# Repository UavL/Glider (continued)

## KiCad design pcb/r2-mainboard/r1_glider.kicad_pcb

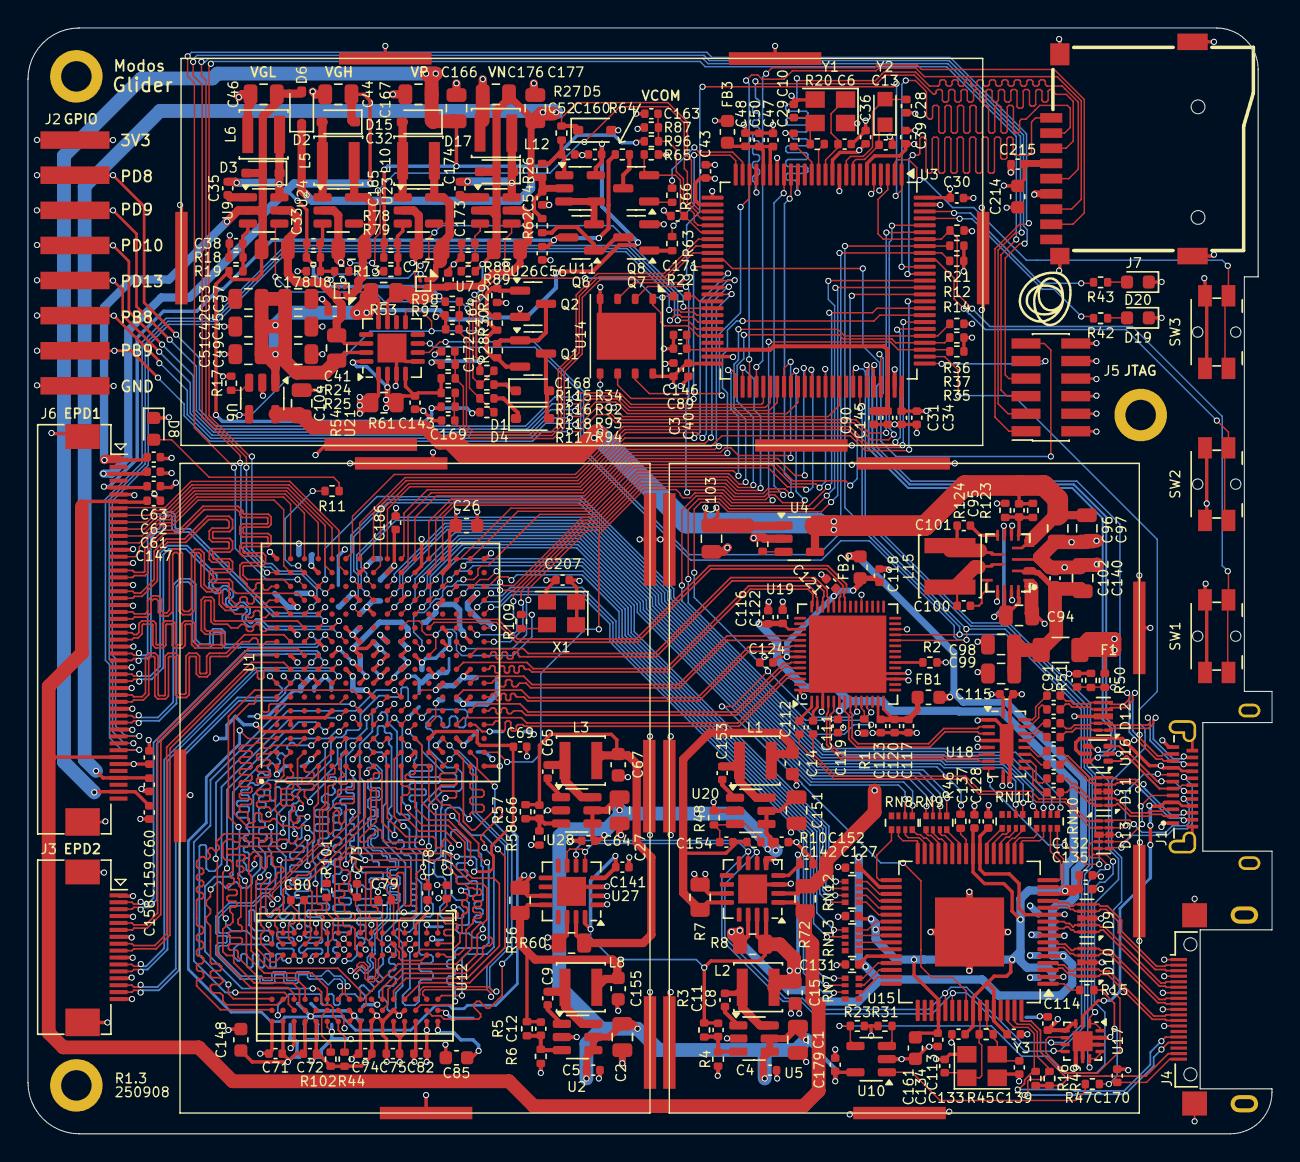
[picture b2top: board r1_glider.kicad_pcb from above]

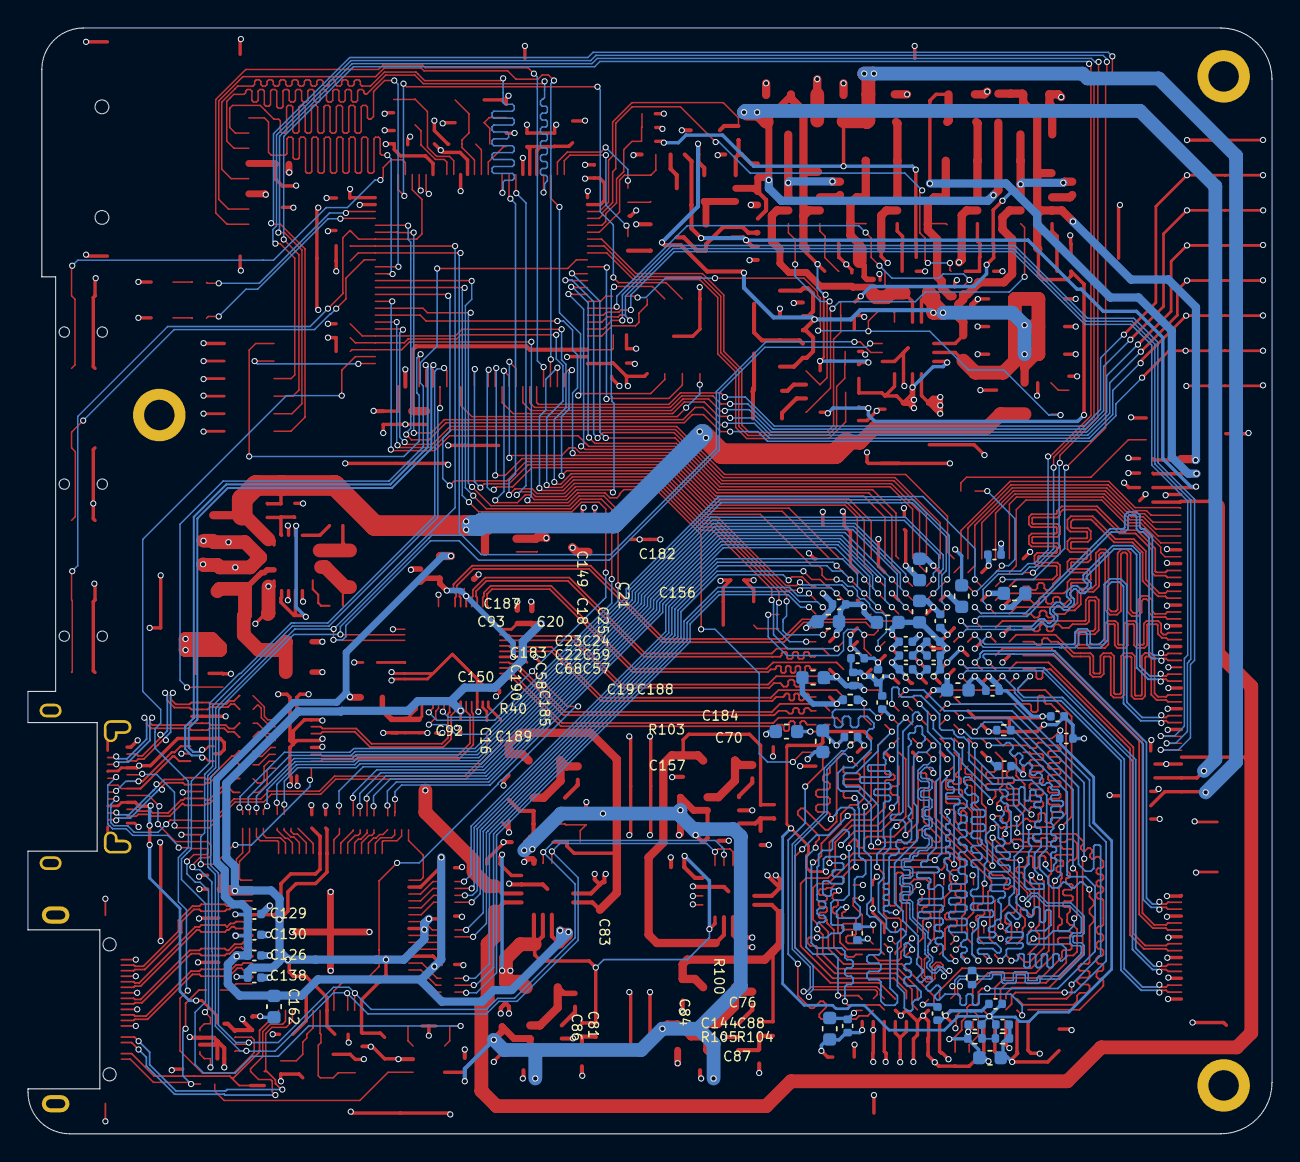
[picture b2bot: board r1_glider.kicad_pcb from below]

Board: 4 copper layers, 90.0 x 80.0 mm, 378 parts (46 on the bottom side), 356 nets.

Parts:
C1, C2, C17, C27, C32, C37, C42, C45, C49, C51, C53, C94, C96, C97, C103, C104, C151: 22uF/10V; C_0805_2012Metric
C3, C4, C5, C7, C8, C9, C29, C30, C31, C35, C36, C39, C40, C43, C48, C50, C54, C55, C60, C61, C62, C63, C64, C65, C71, C72, C74, C75, C76, C77, C78, C88, C100, C101, C102, C105, C106, C107, C108, C109, C110, C111, C112, C114, C115, C119, C120, C121, C122, C123, C124, C127, C128, C129, C130, C131, C133, C134, C135, C136, C137, C138, C139, C141, C142, C143, C144, C147, C152, C153, C158, C159, C160, C171, C174, C179, C215: 100nF/50V; C_0402_1005Metric
C6, C10, C11, C12, C13, C28, C38, C41, C66, C113, C125, C154, C165, C175: 18pF/50V; C_0402_1005Metric
C14, C15, C16, C18, C19, C20, C21, C26, C67, C85, C86, C87, C92, C93, C148, C149, C150, C155, C156, C161, C162, C214: 22uF/6.3V; C_0603_1608Metric
C22, C23, C24, C34, C47, C56, C57, C59, C89, C90, C116, C117, C118, C126, C132, C145, C146, C157, C182, C183, C184: 4.7uF/6.3V; C_0402_1005Metric
C25, C52, C58, C68, C69, C70, C73, C79, C80, C81, C82, C83, C84, C172, C178, C185, C186, C187, C188, C189, C190, C207: 470nF/25V; C_0402_1005Metric
C33, C44, C46, C98, C99, C140, C166, C167, C173, C176, C177: 4.7uF/50V; C_0805_2012Metric
C91, C95, C170: 1nF/50V; C_0402_1005Metric
C163, C164, C168, C169: 1nF/25V; C_0402_1005Metric
D1, D2, D3, D4, D5, D6, D15, D17: 1N5819WS; D_SOD-323_Alt
D8, D19: LED GREEN; LED_0603_1608Metric
D9, D10, D11, D12, D13: RCLAMP0524P; Diodes_UDFN-10_1.0x2.5mm_P0.5mm
D20: LED RED; LED_0603_1608Metric
F1: 3A; Fuse_1206_3216Metric
FB1, FB2, FB3: 120R@100M; L_0603_1608Metric
H1, H3, H4: MountingHole; MountingHole_2.2mm_M2_DIN965_Pad
H5, H6, H7, H8, H9, H12, H13, H14, H15, H16, H17, H18, H19, H20, H21, H22, H23, H25, H26: ICSRC6508-030SFR
J1: GT-USB-7007A; USB_C_Receptacle_GT-USB-7007A
J2: Conn_01x08_MountingPin; 8P_2.54
J3: FPC-05F-16PH20; Xunpu_FPC-05F-16PH20_1x16-1MP_P0.50mm_Horizontal
J4: HDMI_C_1.3; HDMI_C_GT-HD006A-CGNGX
J5: 2x6_1.27_HDR; PinSocket_2x06_P1.27mm_Vertical_SMD
J6: FPC-05F-50PH20; Xunpu_FPC-05F-50PH20_1x50-1MP_P0.50mm_Horizontal
J7: MICRO_SD(TFC-WPAPR-08); TFC-WPAPR-08
L1, L2, L3, L5, L6, L8, L10, L12: WPN3012H4R7MT; L_Changjiang_FNR3012S
L15: WPN4020H2R2MT; L_Changjiang_FNR4020S
Q1, Q7, Q8: AO3401A; SOT-23
Q2: S8050; SOT-23
Q6: AO3400A; SOT-23
R1, R2, R9, R29, R30, R35, R36, R44, R101, R103: 5.1K/1%; R_0402_1005Metric
R3, R13, R26, R28, R34, R51, R57, R58, R62, R87, R92, R93, R94, R97, R116, R118, R124: 100K/1%; R_0402_1005Metric
R4, R25, R27, R64, R89: 22K/1%; R_0402_1005Metric
R5, R78: 150K/1%; R_0402_1005Metric
R6, R48: 120K/1%; R_0402_1005Metric
R7, R8, R53, R54, R56, R60, R61, R72: 20mR; R_0805_2012Metric
R10, R18: 240K/1%; R_0402_1005Metric
R11, R12, R14, R16, R17, R19, R21, R23, R31, R42, R47, R49, R65: 10K/1%; R_0402_1005Metric
R15, R40, R100: 100R/1%; R_0402_1005Metric
R20, R22, R37, R43, R104, R105: 1K/1%; R_0402_1005Metric
R24, R88: 390K/1%; R_0402_1005Metric
R45, R50, R96, R98, R115, R117: 1M/1%; R_0402_1005Metric
R46, R63, R66, R109: 33R/1%; R_0402_1005Metric
R79: 13K/1%; R_0402_1005Metric
R102: 240R/1%; R_0402_1005Metric
R123: 470K/1%; R_0402_1005Metric
RN7, RN8, RN9, RN10, RN11, RN12, RN13: 33R / 4D02WGF330JTCE; R_Array_Convex_4x0402
SW1, SW2, SW3: SW; Panasonic_EVQPUL_EVQPUC
U1: XC6SLX-FTG256; Xilinx_FTG256
U2, U5, U20, U28: SY8113C; TSOT-23-6
U3: STM32H750VBTx; LQFP-100_14x14mm_P0.5mm
U4, U6, U10: MT9700; SOT-23-5
U7, U8: TPS22914BYFPR; WLP-4_0.83x0.83mm_P0.4mm
U9, U26: LGS5145; TSOT-23-6
U11: LM321; SOT-23-5
U12: MT41K64M16TW; BGA-96_9.0x14.0mm_P0.8mm
U13: JW3651QFNE; QFN15_3X4_JW3651
U14: W25Q32JV; WSON-8-1EP_6x5mm_P1.27mm_EP3.4x4.3mm
U15: ADV7611; LQFP-64-1EP_10x10mm_P0.5mm_EP5x5mm
U16: USBLC6-2P6; SOT-666-Alt
U17: FUSB302BMPX; WQFN-14-1EP_2.5x2.5mm_P0.5mm_EP1.45x1.45mm
U18: CBTL02043A; WQFN-20-1EP_2.5x4.5mm_P0.5mm_EP1x2.9mm
U19: PTN3460; QFN-56-1EP_7x7mm_P0.4mm_EP5.6x5.6mm
U21, U22, U27: INA3221; Texas_RGV0016A_VQFN-16-1EP_4x4mm_P0.65mm_EP2.1x2.1mm
U23, U24: LGS6302B5; SOT-23-5
X1: 33.33MHz; Oscillator_SMD_Abracon_ASE-4Pin_3.2x2.5mm
Y1, Y3: 24MHz; Crystal_SMD_3225-4Pin_3.2x2.5mm
Y2: 32.768K; Crystal_SMD_TXC_9HT11-2Pin_2.0x1.2mm_HandSoldering

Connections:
+1V2_DCDC: C66.1, C67.1, L3.2, R57.1, R60.2, U27.15 (IN+2)
+1V2_FPGA: C18.1, C20.1, C22.1, C24.1, C57.1, C59.1, C68.1, R60.1, U1.G7 (VCCINT), U1.G9 (VCCINT), U1.H8 (VCCINT), U1.H10 (VCCINT), U1.J7 (VCCINT), U1.J9 (VCCINT), U1.K8 (VCCINT), U1.K10 (VCCINT), U27.14 (IN-2)
+1V8_DCDC: C14.1, C154.1, L1.2, R7.2, R10.1, U22.12 (IN+1)
+1V8_VID: C116.1, C119.1, C122.1, C132.1, C133.1, C134.1, C135.1, C136.1, C137.1, C138.1, C139.1, C161.1, R7.1, U15.2 (CVDD), U15.14 (CVDD), U15.24 (DVDD), U15.40 (DVDD), U15.52 (DVDD), U15.57 (PVDD), U15.60 (DVDD), U19.6 (VDD18), U19.45 (VDD18), U22.11 (IN-1)
+1V35: C16.1, C71.1, C72.1, C74.1, C75.1, C77.1, C78.1, C79.1, C80.1, C81.1, C82.1, C83.1, C84.1, C85.1, C86.1, C87.1, C88.1, C148.1, C157.1, C185.1, C189.1, R56.1, R104.1, U1.D2 (VCCO_3), U1.G4 (VCCO_3), U1.J2 (VCCO_3), U1.K4 (VCCO_3), U1.N2 (VCCO_3), U12.A1 (VDDQ), U12.A8 (VDDQ), U12.B2 (VDD), U12.C1 (VDDQ), U12.C9 (VDDQ), U12.D2 (VDDQ), U12.D9 (VDD), U12.E9 (VDDQ), U12.F1 (VDDQ), U12.G7 (VDD), U12.H2 (VDDQ), U12.H9 (VDDQ), U12.K2 (VDD), U12.K8 (VDD), U12.N1 (VDD), U12.N9 (VDD), U12.R1 (VDD), U12.R9 (VDD), U27.11 (IN-1)
+1V35_DCDC: C12.1, C155.1, L8.2, R5.1, R56.2, U27.12 (IN+1)
+3V3: C3.1, C19.1, C21.1, C23.1, C25.1, C26.1, C30.1, C31.1, C34.1, C36.1, C39.1, C40.1, C43.1, C58.1, C60.1, C92.1, C93.1, C114.1, C115.1, C149.1, C150.1, C156.1, C182.1, C183.1, C184.1, C186.1, C187.1, C188.1, C190.1, C207.2, C214.1, C215.1, FB3.1, J2.1, J5.12, J6.6, J6.45, J7.4 (VDD), Q7.2 (S), R12.1, R14.1, R35.1, R37.1, R61.1, R65.1, SW1.2, SW2.2, SW3.2, U1.B4 (VCCO_0), U1.B9 (VCCO_0), U1.B13 (VCCO_0), U1.D7 (VCCO_0), U1.D10 (VCCO_0), U1.D15 (VCCO_1), U1.E5 (VCCAUX), U1.F8 (VCCAUX), U1.F11 (VCCAUX), U1.G10 (VCCAUX), U1.G13 (VCCO_1), U1.H6 (VCCAUX), U1.J10 (VCCAUX), U1.J15 (VCCO_1), U1.K13 (VCCO_1), U1.L6 (VCCAUX), U1.L9 (VCCAUX), U1.N7 (VCCO_2), U1.N10 (VCCO_2), U1.N11 (IO_L13P_M1_2), U1.N15 (VCCO_1), U1.R4 (VCCO_2), U1.R8 (VCCO_2), U1.R13 (VCCO_1), U1.T11 (IO_L1N_M0_CMPMISO_2), U3.6 (VBAT), U3.11 (VDD), U3.27 (VDD), U3.50 (VDD), U3.75 (VDD), U3.100 (VDD), U14.8 (VCC), U17.3 (VDD), U17.4 (VDD), U18.1 (VDD), U18.6 (VDD), U18.10 (VDD), U21.1 (IN-3), U22.5 (A0), X1.1 (EN), X1.4 (Vdd)
+3V3A: C47.1, C48.1, C50.1, FB3.2, U3.20 (VREF+), U3.21 (VDDA)
+3V3_DCDC: C11.1, C15.1, C141.1, C142.1, C143.1, L2.2, R3.1, R8.2, R61.2, R116.2, R118.2, U21.2 (IN+3), U21.4 (VS), U21.16 (VPU), U22.4 (VS), U22.15 (IN+2), U22.16 (VPU), U27.4 (VS), U27.16 (VPU)
+3V3_VID: C126.1, C127.1, C128.1, C129.1, C130.1, C131.1, C162.1, FB1.1, FB2.1, R8.1, U15.5 (TVDD), U15.8 (TVDD), U15.11 (TVDD), U15.23 (DVDDIO), U15.34 (DVDDIO), U15.44 (DVDDIO), U22.14 (IN-2)
+5V: C1.2, C2.2, C4.2, C5.2, C27.2, C64.2, C103.2, C151.2, C152.2, C179.1, U2.4 (~SHDN), U2.5 (IN), U4.1 (VOUT), U5.4 (~SHDN), U5.5 (IN), U10.5 (VIN), U20.4 (~SHDN), U20.5 (IN), U28.4 (~SHDN), U28.5 (IN)
+5V2_FL: C147.1, J6.7, J6.44, R72.1, U22.1 (IN-3)
+5V_DCDC: C95.1, C96.2, C97.2, C104.2, R72.2, R123.1, U4.4 (EN), U4.5 (VIN), U6.5 (VIN), U13.4 (VO), U22.2 (IN+3)
+5V_EG: C33.2, C178.1, R54.2, U8.A2 (IN), U9.5 (IN), U21.14 (IN-2)
+5V_EPD: C37.2, C42.2, C45.2, C49.2, C51.2, C53.2, C160.2, Q1.2 (S), R28.2, R30.1, R53.1, R54.1, U6.1 (VOUT), U11.5 (V+), U21.12 (IN+1), U21.15 (IN+2)
+5V_ES: C172.1, C173.2, R53.2, U7.A2 (IN), U21.11 (IN-1), U26.5 (IN)
+5V_HDMI: J4.18 (+5V), R16.2, R49.2, U15.64 (RXA_5V)
+DRAM_VREF: C69.1, C70.1, C73.1, C76.1, C88.2, C144.1, R104.2, R105.1, U1.A3 (IO_L83N_VREF_3), U1.M3 (IO_L1N_VREF_3), U12.H1 (VrefDQ), U12.M8 (VrefCA)
+VBUS: F1.1, J1.A4 (VBUS), J1.A9 (VBUS), J1.B4 (VBUS), J1.B9 (VBUS), R50.1, U16.5 (VBUS), U17.2 (VBUS)
+VGH: C41.2, C44.2, C62.1, D2.1 (K), J6.3, R24.2, R98.2
+VP: C158.1, C165.2, C166.2, C167.2, D15.1 (K), J6.49, R78.2, R96.2
-VCOM: C56.2, C61.1, J6.5, Q6.3 (D), R64.2
-VGL: C33.1, C46.1, C63.1, D3.2 (A), D6.2 (A), J6.1, R19.1, R94.1, R117.1, U9.2 (GND)
-VN: C54.2, C159.1, C173.1, C176.1, C177.1, D6.1 (K), D17.2 (A), J6.47, R26.1, R34.1, R62.2, R89.1, R115.1, U11.2 (V-), U26.2 (GND)
/dp_in/CC1: D13.4 (IO3), D13.7 (NC2), J1.A5 (CC1), U17.10 (CC1), U17.11 (CC1)
/dp_in/CC2: D13.5 (IO4), D13.6 (NC1), J1.B5 (CC2), U17.1 (CC2), U17.14 (CC2)
/dp_in/DP0N: U18.7 (A1_P), U19.5 (DP0_N)
/dp_in/DP0P: U18.8 (A1_N), U19.4 (DP0_P)
/dp_in/DP1N: U18.3 (A0_P), U19.8 (DP1_N)
/dp_in/DP1P: U18.4 (A0_N), U19.7 (DP1_P)
/dp_in/DPAUXN: C112.2, U19.1 (AUX_N)
/dp_in/DPAUXP: C111.2, U19.2 (AUX_P)
/dp_in/RX1N: C105.1, D11.2 (IO2), D11.9 (NC3), J1.A3 (TX1-)
/dp_in/RX1NC: C105.2, U18.13 (C1_P)
/dp_in/RX1P: C106.1, D11.1 (IO1), D11.10 (NC4), J1.A2 (TX1+)
/dp_in/RX1PC: C106.2, U18.12 (C1_N)
/dp_in/RX2N: C109.1, D12.2 (IO2), D12.9 (NC3), J1.B3 (TX2-)
/dp_in/RX2NC: C109.2, U18.17 (B1_P)
/dp_in/RX2P: C110.1, D12.1 (IO1), D12.10 (NC4), J1.B2 (TX2+)
/dp_in/RX2PC: C110.2, U18.16 (B1_N)
/dp_in/SBU1: C112.1, D13.2 (IO2), D13.9 (NC3), J1.A8 (SBU1)
/dp_in/SBU2: C111.1, D13.1 (IO1), D13.10 (NC4), J1.B8 (SBU2)
/dp_in/TX1N: C7.1, D11.5 (IO4), D11.6 (NC1), J1.B10 (RX1-)
/dp_in/TX1NC: C7.2, U18.15 (C0_P)
/dp_in/TX1P: C55.1, D11.4 (IO3), D11.7 (NC2), J1.B11 (RX1+)
/dp_in/TX1PC: C55.2, U18.14 (C0_N)
/dp_in/TX2N: C107.1, D12.5 (IO4), D12.6 (NC1), J1.A10 (RX2-)
/dp_in/TX2NC: C107.2, U18.19 (B0_P)
/dp_in/TX2P: C108.1, D12.4 (IO3), D12.7 (NC2), J1.A11 (RX2+)
/dp_in/TX2PC: C108.2, U18.18 (B0_N)
/epd_power/+5V_VGH: C32.2, L5.1, U8.A1 (OUT), U24.4 (EN), U24.5 (IN)
/epd_power/+5V_VSH: C17.2, L10.1, U7.A1 (OUT), U23.4 (EN), U23.5 (IN)
/epd_power/EN_VGL: R93.1, R94.2, U9.4 (~SHDN)
/epd_power/EN_VN: R34.2, R92.1, U26.4 (~SHDN)
/fpga_ddr/DRAM_ADDR0: U1.K5 (IO_L47P_M3A0_3), U12.N3 (A0)
/fpga_ddr/DRAM_ADDR1: U1.K6 (IO_L47N_M3A1_3), U12.P7 (A1)
/fpga_ddr/DRAM_ADDR2: U1.D1 (IO_L49N_M3A2_3), U12.P3 (A2)
/fpga_ddr/DRAM_ADDR3: U1.L4 (IO_L45P_M3A3_3), U12.N2 (A3)
/fpga_ddr/DRAM_ADDR4: U1.G5 (IO_L51N_M3A4_3), U12.P8 (A4)
/fpga_ddr/DRAM_ADDR5: U1.H4 (IO_L44P_GCLK21_M3A5_3), U12.P2 (A5)
/fpga_ddr/DRAM_ADDR6: U1.H3 (IO_L44N_GCLK20_M3A6_3), U12.R8 (A6)
/fpga_ddr/DRAM_ADDR7: U1.D3 (IO_L49P_M3A7_3), U12.R2 (A7)
/fpga_ddr/DRAM_ADDR8: U1.B2 (IO_L52P_M3A8_3), U12.T8 (A8)
/fpga_ddr/DRAM_ADDR9: U1.A2 (IO_L52N_M3A9_3), U12.R3 (A9)
/fpga_ddr/DRAM_ADDR10: U1.G6 (IO_L51P_M3A10_3), U12.L7 (A10)
/fpga_ddr/DRAM_ADDR11: U1.E3 (IO_L54N_M3A11_3), U12.R7 (A11)
/fpga_ddr/DRAM_ADDR12: U1.F3 (IO_L53N_M3A12_3), U12.N7 (A12/~BC)
/fpga_ddr/DRAM_ADDR13: U1.F6 (IO_L55P_M3A13_3), U12.T3 (A13)
/fpga_ddr/DRAM_ADDR14: U1.F5 (IO_L55N_M3A14_3), U12.T7 (A14/NC)
/fpga_ddr/DRAM_BA0: U1.C3 (IO_L48P_M3BA0_3), U12.M2 (BA0)
/fpga_ddr/DRAM_BA1: U1.C2 (IO_L48N_M3BA1_3), U12.N8 (BA1)
/fpga_ddr/DRAM_BA2: U1.B1 (IO_L50N_M3BA2_3), U12.M3 (BA2)
/fpga_ddr/DRAM_CASB: U1.H5 (IO_L43N_GCLK22_IRDY2_M3CASN_3), U12.K3 (~CAS)
/fpga_ddr/DRAM_CKE: R44.1, U1.F4 (IO_L53P_M3CKE_3), U12.K9 (CKE)
/fpga_ddr/DRAM_CKN: R100.1, U1.E1 (IO_L46N_M3CLKN_3), U12.K7 (~CK)
/fpga_ddr/DRAM_CKP: R100.2, U1.E2 (IO_L46P_M3CLK_3), U12.J7 (CK)
/fpga_ddr/DRAM_CSB: R101.1, U12.L2 (~CS)
/fpga_ddr/DRAM_DATA0: U1.K2 (IO_L37P_M3DQ0_3), U12.E3 (DQ0)
/fpga_ddr/DRAM_DATA1: U1.K1 (IO_L37N_M3DQ1_3), U12.F7 (DQ1)
/fpga_ddr/DRAM_DATA2: U1.J3 (IO_L38P_M3DQ2_3), U12.F2 (DQ2)
/fpga_ddr/DRAM_DATA3: U1.J1 (IO_L38N_M3DQ3_3), U12.F8 (DQ3)
/fpga_ddr/DRAM_DATA4: U1.F2 (IO_L41P_GCLK27_M3DQ4_3), U12.H3 (DQ4)
/fpga_ddr/DRAM_DATA5: U1.F1 (IO_L41N_GCLK26_M3DQ5_3), U12.H8 (DQ5)
/fpga_ddr/DRAM_DATA6: U1.G3 (IO_L40P_M3DQ6_3), U12.G2 (DQ6)
/fpga_ddr/DRAM_DATA7: U1.G1 (IO_L40N_M3DQ7_3), U12.H7 (DQ7)
/fpga_ddr/DRAM_DATA8: U1.L3 (IO_L36P_M3DQ8_3), U12.D7 (DQ8)
/fpga_ddr/DRAM_DATA9: U1.L1 (IO_L36N_M3DQ9_3), U12.C3 (DQ9)
/fpga_ddr/DRAM_DATA10: U1.M2 (IO_L35P_M3DQ10_3), U12.C8 (DQ10)
/fpga_ddr/DRAM_DATA11: U1.M1 (IO_L35N_M3DQ11_3), U12.C2 (DQ11)
/fpga_ddr/DRAM_DATA12: U1.P2 (IO_L33P_M3DQ12_3), U12.A7 (DQ12)
/fpga_ddr/DRAM_DATA13: U1.P1 (IO_L33N_M3DQ13_3), U12.A2 (DQ13)
/fpga_ddr/DRAM_DATA14: U1.R2 (IO_L32P_M3DQ14_3), U12.B8 (DQ14)
/fpga_ddr/DRAM_DATA15: U1.R1 (IO_L32N_M3DQ15_3), U12.A3 (DQ15)
/fpga_ddr/DRAM_LDM: U1.J4 (IO_L42N_GCLK24_M3LDM_3), U12.E7 (LDM)
/fpga_ddr/DRAM_LDQSN: U1.H1 (IO_L39N_M3LDQSN_3), U12.G3 (~LDQS)
/fpga_ddr/DRAM_LDQSP: U1.H2 (IO_L39P_M3LDQS_3), U12.F3 (LDQS)
/fpga_ddr/DRAM_ODT: U1.L5 (IO_L45N_M3ODT_3), U12.K1 (ODT)
/fpga_ddr/DRAM_RASB: U1.J6 (IO_L43P_GCLK23_M3RASN_3), U12.J3 (~RAS)
/fpga_ddr/DRAM_RST: R103.1, U1.E4 (IO_L54P_M3RESET_3), U12.T2 (~RESET)
/fpga_ddr/DRAM_UDM: U1.K3 (IO_L42P_GCLK25_TRDY2_M3UDM_3), U12.D3 (UDM)
/fpga_ddr/DRAM_UDQSN: U1.N1 (IO_L34N_M3UDQSN_3), U12.B7 (~UDQS)
/fpga_ddr/DRAM_UDQSP: U1.N3 (IO_L34P_M3UDQS_3), U12.C7 (UDQS)
/fpga_ddr/DRAM_WEB: U1.C1 (IO_L50P_M3WE_3), U12.L3 (~WE)
/fpga_io/LED: R11.1, U1.C15 (IO_L33P_A15_M1A10_1)
/mcu/G_LED: R42.1, U3.97 (PE0)
/mcu/OSC32_IN: C13.1, U3.8 (PC14), Y2.1
/mcu/OSC32_OUT: C28.1, U3.9 (PC15), Y2.2
/mcu/OSC_IN: C6.1, U3.12 (PH0), Y1.1
/mcu/OSC_OUT: R20.1, U3.13 (PH1)
/mcu/R_LED: R43.1, U3.98 (PE1)
/power/EVDD: C94.2, U13.7 (EN), U13.13 (VCC), U13.15 (CSN)
/tmds_in/ADV_CK: R46.2, U15.25 (LLC)
/tmds_in/ADV_DE: RN7.4 (R4.1), U15.45 (DE)
/tmds_in/ADV_HS: RN7.3 (R3.1), U15.46 (HS)
/tmds_in/ADV_P0: RN13.1 (R1.1), U15.43 (P0)
/tmds_in/ADV_P1: RN13.2 (R2.1), U15.42 (P1)
/tmds_in/ADV_P2: RN13.3 (R3.1), U15.41 (P2)
/tmds_in/ADV_P3: RN13.4 (R4.1), U15.39 (P3)
/tmds_in/ADV_P4: RN12.1 (R1.1), U15.38 (P4)
/tmds_in/ADV_P5: RN12.2 (R2.1), U15.37 (P5)
/tmds_in/ADV_P6: RN12.3 (R3.1), U15.36 (P6)
/tmds_in/ADV_P7: RN12.4 (R4.1), U15.35 (P7)
/tmds_in/ADV_P8: RN8.1 (R1.1), U15.33 (P8)
/tmds_in/ADV_P9: RN8.2 (R2.1), U15.32 (P9)
/tmds_in/ADV_P10: RN8.3 (R3.1), U15.31 (P10)
/tmds_in/ADV_P11: RN8.4 (R4.1), U15.30 (P11)
/tmds_in/ADV_P12: RN9.1 (R1.1), U15.29 (P12)
/tmds_in/ADV_P13: RN9.2 (R2.1), U15.28 (P13)
/tmds_in/ADV_P14: RN9.3 (R3.1), U15.27 (P14)
/tmds_in/ADV_P15: RN9.4 (R4.1), U15.26 (P15)
/tmds_in/ADV_P16: RN11.1 (R1.1), U15.22 (P16)
/tmds_in/ADV_P17: RN11.2 (R2.1), U15.21 (P17)
/tmds_in/ADV_P18: RN11.3 (R3.1), U15.20 (P18)
/tmds_in/ADV_P19: RN11.4 (R4.1), U15.19
/tmds_in/ADV_P20: RN10.1 (R1.1), U15.18 (P20)
/tmds_in/ADV_P21: RN10.2 (R2.1), U15.17 (P21)
/tmds_in/ADV_P22: RN10.3 (R3.1), U15.16 (P22)
/tmds_in/ADV_P23: RN10.4 (R4.1), U15.15 (P23)
/tmds_in/ADV_VS: RN7.2 (R2.1), U15.47 (VS/FIELD/ALSB)
/tmds_in/HDMI_HPD: C170.1, J4.19 (HPD), R15.2, R47.2
/tmds_in/HDMI_SCL: J4.15 (SCL), R16.1, U15.62 (DDCA_SCL)
/tmds_in/HDMI_SDA: J4.16 (SDA), R49.1, U15.63 (DDCA_SDA)
/tmds_in/TMDS_CKN: D10.1 (IO1), D10.10 (NC4), J4.12 (CK-), U15.3 (RXA_C-)
/tmds_in/TMDS_CKP: D10.2 (IO2), D10.9 (NC3), J4.11 (CK+), U15.4 (RXA_C+)
/tmds_in/TMDS_D0N: D10.4 (IO3), D10.7 (NC2), J4.9 (D0-), U15.6 (RXA_0-)
/tmds_in/TMDS_D0P: D10.5 (IO4), D10.6 (NC1), J4.8 (D0+), U15.7 (RXA_0+)
/tmds_in/TMDS_D1N: D9.1 (IO1), D9.10 (NC4), J4.6 (D1-), U15.9 (RXA_1-)
/tmds_in/TMDS_D1P: D9.2 (IO2), D9.9 (NC3), J4.5 (D1+), U15.10 (RXA_1+)
/tmds_in/TMDS_D2N: D9.4 (IO3), D9.7 (NC2), J4.3 (D2-), U15.12 (RXA_2-)
/tmds_in/TMDS_D2P: D9.5 (IO4), D9.6 (NC1), J4.2 (D2+), U15.13 (RXA_2+)
DEC_RST: U3.87 (PD6), U15.56 (~RESET), U19.9 (RST_N)
DPI_B2: RN13.6 (R3.2), U1.T14 (IO_L51P_M1DQ12_1)
DPI_B3: RN13.5 (R4.2), U1.R14 (IO_L50P_M1UDQS_1)
DPI_B4: RN12.8 (R1.2), U1.N14 (IO_L45P_A1_M1LDQS_1)
DPI_B5: RN12.7 (R2.2), U1.P15 (IO_L48P_HDC_M1DQ8_1)
DPI_B6: RN12.6 (R3.2), U1.M13 (IO_L74P_AWAKE_1)
DPI_B7: RN12.5 (R4.2), U1.M14 (IO_L74N_DOUT_BUSY_1)
DPI_DE: RN7.5 (R4.2), U1.T13 (IO_L51N_M1DQ13_1)
DPI_G2: RN8.6 (R3.2), U1.L12 (IO_L53P_1)
DPI_G3: RN8.5 (R4.2), U1.L13 (IO_L53N_VREF_1)
DPI_G4: RN9.8 (R1.2), U1.L14 (IO_L47P_FWE_B_M1DQ0_1)
DPI_G5: RN9.7 (R2.2), U1.K12 (IO_L42P_GCLK7_M1UDM_1)
DPI_G6: RN9.6 (R3.2), U1.K14 (IO_L41N_GCLK8_M1CASN_1)
DPI_G7: RN9.5 (R4.2), U1.J12 (IO_L40N_GCLK10_M1A6_1)
DPI_HS: RN7.6 (R3.2), U1.R12 (IO_L52P_M1DQ14_1)
DPI_PCLK: R46.1, U1.J13 (IO_L41P_GCLK9_IRDY1_M1RASN_1)
DPI_R2: RN11.6 (R3.2), U1.J14 (IO_L43P_GCLK5_M1DQ4_1)
DPI_R3: RN11.5 (R4.2), U1.H14 (IO_L39N_M1ODT_1)
DPI_R4: RN10.8 (R1.2), U1.H13 (IO_L39P_M1A3_1)
DPI_R5: RN10.7 (R2.2), U1.G12 (IO_L38P_A5_M1CLK_1)
DPI_R6: RN10.6 (R3.2), U1.G14 (IO_L36P_A9_M1BA0_1)
DPI_R7: RN10.5 (R4.2), U1.D14 (IO_L31P_A19_M1CKE_1)
DPI_VS: RN7.7 (R2.2), U1.T12 (IO_L52N_M1DQ15_1)
DP_HPD: U3.88 (PD7), U19.11 (HPDRX)
DP_PDN: R1.2, U3.84 (PD3), U19.10 (PD_N)
EPDC_CLKN: J3.2, U1.D8 (IO_L38P_0)
EPDC_CLKP: J3.3, U1.C8 (IO_L38N_VREF_0)
EPDC_D0N: J6.38, U1.C10 (IO_L37N_GCLK12_0)
EPDC_D0P: J6.39, U1.E10 (IO_L37P_GCLK13_0)
EPDC_D1N: J6.35, U1.B10 (IO_L35P_GCLK17_0)
EPDC_D1P: J6.36, U1.A10 (IO_L35N_GCLK16_0)
EPDC_D2N: J6.32, U1.E11 (IO_L64N_SCP4_0)
EPDC_D2P: J6.33, U1.F10 (IO_L64P_SCP5_0)
EPDC_D3N: J6.29, U1.D12 (IO_L66N_SCP0_0)
EPDC_D3P: J6.30, U1.D11 (IO_L66P_SCP1_0)
EPDC_D4N: J6.26, U1.C11 (IO_L39P_0)
EPDC_D4P: J6.27, U1.A11 (IO_L39N_0)
EPDC_D5N: J6.23, U1.B12 (IO_L62P_0)
EPDC_D5P: J6.24, U1.A12 (IO_L62N_VREF_0)
EPDC_D6N: J6.20, U1.C13 (IO_L63P_SCP7_0)
EPDC_D6P: J6.21, U1.A13 (IO_L63N_SCP6_0)
EPDC_D7N: J6.17, U1.B14 (IO_L65P_SCP3_0)
EPDC_D7P: J6.18, U1.A14 (IO_L65N_SCP2_0)
EPDC_D8N: J3.14, U1.A7 (IO_L6N_0)
EPDC_D8P: J3.15, U1.C7 (IO_L6P_0)
EPDC_D9N: J3.11, U1.E8 (IO_L36N_GCLK14_0)
EPDC_D9P: J3.12, U1.E7 (IO_L36P_GCLK15_0)
EPDC_D10N: J3.8, U1.B8 (IO_L33P_0)
EPDC_D10P: J3.9, U1.A8 (IO_L33N_0)
EPDC_D11N: J3.5, U1.C9 (IO_L34P_GCLK19_0)
EPDC_D11P: J3.6, U1.A9 (IO_L34N_GCLK18_0)
EPDC_GDCLK: J6.13, U1.B16 (IO_L29N_A22_M1A14_1)
EPDC_GDOE: J6.11, U1.D16 (IO_L31N_A18_M1A12_1)
EPDC_GDSP: J6.12, U1.C16 (IO_L33N_A14_M1A4_1)
EPDC_SDCE0: J6.10, U1.E15 (IO_L34P_A13_M1WE_1)
EPDC_SDLE: J6.9, U1.E16 (IO_L34N_A12_M1BA2_1)
EPDC_SDOE: J6.8, U1.F15 (IO_L35P_A11_M1A7_1)
EPDC_SE_CLK: J6.15, U1.B15 (IO_L29P_A23_M1A13_1)
EPD_POS_EN: U3.42 (PE12), U7.B2 (ON), U8.B2 (ON)
EPD_PWR_EN: R22.1, U6.4 (EN), U21.9 (CRITICAL)
EPD_THROT: U1.M16 (IO_L46N_FOE_B_M1DQ3_1), U3.83 (PD2)
FL_EN: J6.43, U3.45 (PE15)
FL_PWM1: J6.41, U3.43 (PE13)
FL_PWM2: J6.42, U3.44 (PE14)
FMC_A16: U1.L16 (IO_L47N_LDC_M1DQ1_1), U3.58 (PD11)
FMC_D0: U1.M15 (IO_L46P_FCS_B_M1DQ2_1), U3.61 (PD14)
FMC_D1: U1.R16 (IO_L49N_M1DQ11_1), U3.62 (PD15)
FMC_D2: U1.F16 (IO_L35N_A10_M1A2_1), U3.81 (PD0)
FMC_D3: U1.G16 (IO_L36N_A8_M1BA1_1), U3.82 (PD1)
FMC_D4: U1.H15 (IO_L37P_A7_M1A0_1), U3.37 (PE7)
FMC_D5: U1.H16 (IO_L37N_A6_M1A1_1), U3.38 (PE8)
FMC_D6: U1.J16 (IO_L43N_GCLK4_M1DQ5_1), U3.39 (PE9)
FMC_D7: U1.K15 (IO_L44P_A3_M1DQ6_1), U3.40 (PE10)
FMC_NE1: U1.P16 (IO_L48N_M1DQ9_1), U3.64 (PC7)
FMC_NOE: U1.K16 (IO_L44N_A2_M1DQ7_1), U3.85 (PD4)
FMC_NWE: U1.N16 (IO_L45N_A0_M1LDQSN_1), U3.86 (PD5)
FPGA_CS: U1.L10 (IO_L16P_2), U3.51 (PB12)
FPGA_DONE: R37.2, U1.P13 (DONE_2), U3.79 (PC11)
FPGA_MISO: U1.T10 (IO_L3N_MOSI_CSI_B_MISO0_2), U3.17 (PC2_C)
FPGA_MOSI: U1.P10 (IO_L3P_D0_DIN_MISO_MISO1_2), U3.18 (PC3_C)
FPGA_PROG: R35.2, U1.T2 (PROGRAM_B_2), U3.78 (PC10)
FPGA_SCLK: U1.R11 (IO_L1P_CCLK_2), U3.52 (PB13)
FPGA_SUSP: R36.1, U1.P14 (SUSPEND), U3.80 (PC12)
FPGA_TCK: J5.1, U1.C14 (TCK)
FPGA_TDI: J5.3, U1.C12 (TDI)
FPGA_TDO: J5.5, U1.E14 (TDO)
FPGA_TMS: J5.7, U1.A15 (TMS)
GCLK: R109.2, U1.K11 (IO_L42N_GCLK6_TRDY1_M1LDM_1), U1.M9 (IO_L29P_GCLK3_2)
GND: C1.1, C2.1, C3.2, C4.1, C5.1, C6.2, C10.2, C13.2, C14.2, C15.2, C16.2, C17.1, C18.2, C19.2, C20.2, C21.2, C22.2, C23.2, C24.2, C25.2, C26.2, C27.1, C28.2, C29.1, C30.2, C31.2, C32.1, C34.2, C36.2, C37.1, C38.2, C39.2, C40.2, C42.1, C43.2, C44.1, C45.1, C46.2, C47.2, C48.2, C49.1, C50.2, C51.1, C52.1, C53.1, C54.1, C56.1, C57.2, C58.2, C59.2, C60.2, C61.2, C62.2, C63.2, C64.1, C67.2, C68.2, C69.2, C70.2, C71.2, C72.2, C73.2, C74.2, C75.2, C76.2, C77.2, C78.2, C79.2, C80.2, C81.2, C82.2, C83.2, C84.2, C85.2, C86.2, C87.2, C89.1, C90.1, C91.2, C92.2, C93.2, C94.1, C96.1, C97.1, C98.1, C99.1, C102.1, C103.1, C104.1, C113.2, C114.2, C115.2, C116.2, C117.2, C118.2, C119.2, C120.2, C121.2, C122.2, C123.2, C124.2, C125.2, C126.2, C127.2, C128.2, C129.2, C130.2, C131.2, C132.2, C133.2, C134.2, C135.2, C136.2, C137.2, C138.2, C139.2, C140.1, C141.2, C142.2, C143.2, C144.2, C145.1, C146.1, C147.2, C148.2, C149.2, C150.2, C151.1, C152.1, C155.2, C156.2, C157.2, C158.2, C159.2, C160.1, C161.2, C162.2, C163.1, C164.1, C166.1, C167.1, C168.1, C169.1, C170.2, C171.1, C172.2, C175.2, C176.2, C177.2, C178.2, C179.2, C182.2, C183.2, C184.2, C185.2, C186.2, C187.2, C188.2, C189.2, C190.2, C207.1, C214.2, C215.2, D5.2 (A), D8.1 (K), D9.3 (GND), D9.8 (GND), D10.3 (GND), D10.8 (GND), D11.3 (GND), D11.8 (GND), D12.3 (GND), D12.8 (GND), D13.3 (GND), D13.8 (GND), D19.1 (K), D20.1 (K), H1.1, H3.1, H4.1, H5.1, H6.1, H7.1, H8.1, H9.1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
HPD_EN: R23.2, U3.68 (PA9), U10.4 (EN)
I2C1_SCL: R14.2, U3.92 (PB6), U15.53 (SCL), U17.6 (SCL), U19.25 (MS_SCL), U21.6 (SCL), U22.6 (SCL), U27.6 (SCL)
I2C1_SDA: R12.2, U3.93 (PB7), U15.54 (SDA), U17.7 (SDA), U19.24 (MS_SDA), U21.7 (SDA), U22.7 (SDA), U27.5 (A0), U27.7 (SDA)
KEY1: R21.2, SW1.1, U3.3 (PE4), U3.94 (BOOT0)
KEY2: SW2.1, U3.91 (PB5)
KEY3: SW3.1, U3.2 (PE3)
LVDS_BKLTEN: U3.4 (PE5), U19.26 (BKLTEN)
LVDS_EVEN_AN: U1.T8 (IO_L30N_GCLK0_USERCCLK_2), U19.42 (LVSAE_N)
LVDS_EVEN_AP: U1.P8 (IO_L30P_GCLK1_D13_2), U19.41 (LVSAE_P)
LVDS_EVEN_BN: U1.T9 (IO_L23N_2), U19.40 (LVSBE_N)
LVDS_EVEN_BP: U1.R9 (IO_L23P_2), U19.39 (LVSBE_P)
LVDS_EVEN_CN: U1.M11 (IO_L2N_CMPMOSI_2), U19.37 (LVSCE_N)
LVDS_EVEN_CP: U1.M12 (IO_L2P_CMPCLK_2), U19.36 (LVSCE_P)
LVDS_ODD_AN: U1.T4 (IO_L63N_2), U19.54 (LVSAO_N)
LVDS_ODD_AP: U1.P4 (IO_L63P_2), U19.53 (LVSAO_P)
LVDS_ODD_BN: U1.T5 (IO_L48N_RDWR_B_VREF_2), U19.52 (LVSBO_N)
LVDS_ODD_BP: U1.R5 (IO_L48P_D7_2), U19.51 (LVSBO_P)
LVDS_ODD_CKN: U1.T7 (IO_L32N_GCLK28_2), U19.47 (LVSCKO_N)
LVDS_ODD_CKP: U1.R7 (IO_L32P_GCLK29_2), U19.46 (LVSCKO_P)
LVDS_ODD_CN: U1.T6 (IO_L47N_2), U19.49 (LVSCO_N)
LVDS_ODD_CP: U1.P6 (IO_L47P_2), U19.48 (LVSCO_P)
LVDS_PVCCEN: U3.5 (PE6), U19.33 (PVCCEN)
MCU_SWCLK: J5.9, U3.76 (PA14)
MCU_SWDIO: J5.11, U3.72 (PA13)
unnamed: C10.1, R20.2, Y1.3
unnamed: C117.1, C120.1, C123.1, FB1.2, U19.13 (VDD33), U19.14 (VDD33)
unnamed: C118.1, C121.1, C124.1, FB2.2, U19.38 (VDD33), U19.50 (VDD33)
unnamed: C89.2, C90.2, C145.2, C146.2, U3.48 (VCAP), U3.73 (VCAP)
unnamed: D1.2 (A), D4.2 (A), Q1.3 (D)
unnamed: D1.1 (K), R92.2
unnamed: D2.2 (A), L5.2, U24.1 (SW)
unnamed: C35.1, D3.1 (K), L6.1, U9.6 (SW)
unnamed: D4.1 (K), R93.2
unnamed: D8.2 (A), R11.2
unnamed: D15.2 (A), L10.2, U23.1 (SW)
unnamed: C174.1, D17.1 (K), L12.1, U26.6 (SW)
unnamed: D19.2 (A), R42.2
unnamed: D20.2 (A), R43.2
unnamed: J1.A6 (D+), J1.B6 (D+), U16.1 (I/O1)
unnamed: J1.A7 (D-), J1.B7 (D-), U16.3 (I/O2)
unnamed: Q1.1 (G), Q2.3 (C), R28.1
unnamed: Q2.1 (B), R29.2, R30.2
unnamed: Q6.1 (G), Q7.3 (D), R62.1
unnamed: Q6.2 (S), U11.3 (-), U11.4
unnamed: Q7.1 (G), R63.2
unnamed: Q8.3 (D), R64.1
unnamed: Q8.1 (G), R66.1
unnamed: R40.1, U1.M4 (IO_L1P_3)
unnamed: C9.2, U2.1 (BS)
unnamed: C12.2, R5.2, R6.1, U2.3 (FB)
unnamed: C9.1, L8.1, U2.6 (SW)
unnamed: C29.2, U3.14 (NRST)
unnamed: R22.2, U3.41 (PE11)
unnamed: R9.2, U4.3 (SET)
unnamed: C8.2, U5.1 (BS)
unnamed: C11.2, R3.2, R4.1, U5.3 (FB)
unnamed: C8.1, L2.1, U5.6 (SW)
unnamed: R17.2, U6.3 (SET)
unnamed: C35.2, U9.1 (BS)
unnamed: C38.1, R18.1, R19.2, U9.3 (FB)
unnamed: R31.2, U10.3 (SET)
unnamed: R47.1, U10.1 (VOUT)
unnamed: C52.2, R26.2, R27.1, U11.1 (+)
unnamed: R102.1, U12.L8 (ZQ)
unnamed: C101.1, U13.8 (BST1)
unnamed: C100.1, U13.11 (BST2)
unnamed: C95.2, R123.2, R124.2, U13.5 (FB)
unnamed: C101.2, L15.2, U13.9 (SW1)
unnamed: C100.2, L15.1, U13.10 (SW2)
unnamed: C98.2, C99.2, C102.2, C140.2, F1.2, U13.2 (VIN)
unnamed: R15.1, U15.1 (HPA_A/INT2)
unnamed: C125.1, R45.1, U15.59 (XTALN), Y3.3
unnamed: C113.1, R45.2, U15.58 (XTALP), Y3.1
unnamed: R2.2, U19.20 (TESTMODE)
unnamed: C153.2, U20.1 (BS)
unnamed: C154.2, R10.2, R48.1, U20.3 (FB)
unnamed: C153.1, L1.1, U20.6 (SW)
unnamed: C165.1, R78.1, R79.2, U23.3 (FB)
unnamed: C41.1, R13.1, R24.1, R25.2, U24.3 (FB)
unnamed: C174.2, U26.1 (BS)
unnamed: C175.1, R88.1, R89.2, U26.3 (FB)
unnamed: C65.2, U28.1 (BS)
unnamed: C66.2, R57.2, R58.1, U28.3 (FB)
unnamed: C65.1, L3.1, U28.6 (SW)
unnamed: R109.1, X1.3 (OUT)
QSPI_SCLK: U3.36 (PB2), U14.6 (CLK)
QSPI_SD0: U3.66 (PC9), U14.5 (DI(IO0))
QSPI_SD1: U3.59 (PD12), U14.2 (DO(IO1))
QSPI_SD2: U3.1 (PE2), U14.3 (IO2)
QSPI_SD3: U3.23 (PA1), U14.7 (IO3)
QSPI_SS: U3.46 (PB10), U14.1 (~CS)
SDIO_CLK: J7.5 (CLK/SCLK), U3.16 (PC1)
SDIO_CMD: J7.3 (CMD/DI), U3.22 (PA0)
SDIO_DAT0: J7.7 (DAT0/DO), U3.53 (PB14)
SDIO_DAT1: J7.8 (DAT1/RES), U3.54 (PB15)
SDIO_DAT2: J7.1 (DAT2/RES), U3.89 (PB3)
SDIO_DAT3: J7.2 (CD/DAT3/CS), U3.90 (PB4)
TCPC_INT: U3.77 (PA15), U17.5 (INT_N)
TYPEC_ORI: U3.69 (PA10), U18.9 (SEL)
USB_DN: U3.70 (PA11), U16.4 (I/O2)
USB_DP: U3.71 (PA12), U16.6 (I/O1)
USER_PB8: J2.6, U3.95 (PB8)
USER_PB9: J2.7, U3.96 (PB9)
USER_PD8: J2.2, U3.55 (PD8)
USER_PD9: J2.3, U3.56 (PD9)
USER_PD10: J2.4, U3.57 (PD10)
USER_PD13: J2.5, U3.60 (PD13)
VBUS_MEA: C91.1, R50.2, R51.1, U3.35 (PB1)
VCOM_DAC: D5.1 (K), R27.2, U3.28 (PA4)
VCOM_EN: R63.1, U3.25 (PA3)
VCOM_MEA: C171.2, Q8.2 (S), R65.2, U3.31 (PA7)
VCOM_MEA_EN: R66.2, U3.24 (PA2)
VGH_DAC: R13.2, U3.29 (PA5)
VGH_MEA: C164.2, R97.2, R98.1, U3.32 (PC4)
VGL_MEA: C169.2, R117.2, R118.1, U3.34 (PB0)
VN_MEA: C168.2, R115.2, R116.1, U3.33 (PC5)
VP_MEA: C163.2, R87.2, R96.1, U3.30 (PA6)

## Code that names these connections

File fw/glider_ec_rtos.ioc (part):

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Mcu.Name=STM32H750VBTx
Mcu.Package=LQFP100
Mcu.UserName=STM32H750VBTx
PA0.Mode=SD_4_bits_Wide_bus
PA0.Signal=SDMMC2_CMD
PA1.GPIOParameters=GPIO_Speed
PA1.GPIO_Speed=GPIO_SPEED_FREQ_VERY_HIGH
PA1.Mode=Single Bank 1
PA1.Signal=QUADSPI_BK1_IO3
PA10.Signal=GPIO_Output
PA11.Mode=Device_Only
PA11.Signal=USB_OTG_FS_DM
PA12.Mode=Device_Only
PA12.Signal=USB_OTG_FS_DP
PA13\ (JTMS/SWDIO).Mode=Serial_Wire
PA13\ (JTMS/SWDIO).Signal=DEBUG_JTMS-SWDIO
PA14\ (JTCK/SWCLK).Mode=Serial_Wire
PA14\ (JTCK/SWCLK).Signal=DEBUG_JTCK-SWCLK
PA15\ (JTDI).GPIOParameters=GPIO_PuPd,GPIO_ModeDefaultEXTI
PA15\ (JTDI).GPIO_ModeDefaultEXTI=GPIO_MODE_IT_FALLING
PA15\ (JTDI).GPIO_PuPd=GPIO_PULLUP
PA15\ (JTDI).Signal=GPXTI15
PA2.GPIOParameters=PinState
PA2.PinState=GPIO_PIN_SET
PA2.Signal=GPIO_Output
PA3.GPIOParameters=PinState
PA3.PinState=GPIO_PIN_SET
PA3.Signal=GPIO_Output
PA4.Signal=COMP_DAC11_group
PA5.Signal=COMP_DAC12_group
PA6.Signal=ADCx_INP3
PA7.Signal=ADCx_INP7
PA9.Signal=GPIO_Output
PB0.Signal=ADCx_INP9
PB1.Signal=ADCx_INP5
PB10.GPIOParameters=GPIO_Speed
PB10.GPIO_Speed=GPIO_SPEED_FREQ_VERY_HIGH
PB10.Mode=Single Bank 1
PB10.Signal=QUADSPI_BK1_NCS
PB12.Signal=GPIO_Output
PB13.GPIOParameters=GPIO_Speed
PB13.GPIO_Speed=GPIO_SPEED_FREQ_HIGH
PB13.Mode=Full_Duplex_Master
PB13.Signal=SPI2_SCK
PB14.Mode=SD_4_bits_Wide_bus
PB14.Signal=SDMMC2_D0
PB15.Mode=SD_4_bits_Wide_bus
PB15.Signal=SDMMC2_D1
PB2.GPIOParameters=GPIO_Speed
PB2.GPIO_Speed=GPIO_SPEED_FREQ_VERY_HIGH
PB2.Mode=Single Bank 1
PB2.Signal=QUADSPI_CLK
PB3\ (JTDO/TRACESWO).Mode=SD_4_bits_Wide_bus
PB3\ (JTDO/TRACESWO).Signal=SDMMC2_D2
PB4\ (NJTRST).Mode=SD_4_bits_Wide_bus
PB4\ (NJTRST).Signal=SDMMC2_D3
PB5.GPIOParameters=GPIO_PuPd
PB5.GPIO_PuPd=GPIO_PULLDOWN
PB5.Signal=GPIO_Input
PB6.Mode=I2C
PB6.Signal=I2C1_SCL
PB7.Mode=I2C
PB7.Signal=I2C1_SDA
PB8.GPIOParameters=GPIO_PuPd
PB8.GPIO_PuPd=GPIO_PULLDOWN
PB8.Signal=GPIO_Input
PC1.Mode=SD_4_bits_Wide_bus
PC1.Signal=SDMMC2_CK
PC10.Signal=GPIO_Output
PC11.GPIOParameters=GPIO_PuPd
PC11.GPIO_PuPd=GPIO_PULLUP
PC11.Signal=GPIO_Input
PC12.Signal=GPIO_Output
PC14-OSC32_IN\ (OSC32_IN).Mode=LSE-External-Oscillator
PC14-OSC32_IN\ (OSC32_IN).Signal=RCC_OSC32_IN
PC15-OSC32_OUT\ (OSC32_OUT).Mode=LSE-External-Oscillator
PC15-OSC32_OUT\ (OSC32_OUT).Signal=RCC_OSC32_OUT
PC2_C.GPIOParameters=GPIO_Speed
PC2_C.GPIO_Speed=GPIO_SPEED_FREQ_HIGH
PC2_C.Mode=Full_Duplex_Master
PC2_C.Signal=SPI2_MISO
PC3_C.GPIOParameters=GPIO_Speed
PC3_C.GPIO_Speed=GPIO_SPEED_FREQ_HIGH
PC3_C.Mode=Full_Duplex_Master
PC3_C.Signal=SPI2_MOSI
PC4.Signal=ADCx_INP4
PC5.Signal=ADCx_INP8
PC7.Mode=NorPsramChipSelect1_1
PC7.Signal=FMC_NE1
PC9.GPIOParameters=GPIO_Speed
PC9.GPIO_Speed=GPIO_SPEED_FREQ_VERY_HIGH
PC9.Mode=Single Bank 1
PC9.Signal=QUADSPI_BK1_IO0
PD0.Signal=FMC_D2_DA2
PD1.Signal=FMC_D3_DA3
PD11.Signal=FMC_A16_CLE
PD12.GPIOParameters=GPIO_Speed
PD12.GPIO_Speed=GPIO_SPEED_FREQ_VERY_HIGH
PD12.Mode=Single Bank 1
PD12.Signal=QUADSPI_BK1_IO1
PD14.Signal=FMC_D0_DA0
PD15.Signal=FMC_D1_DA1
PD2.Signal=GPIO_Output
PD3.Signal=GPIO_Output
PD4.Signal=FMC_NOE
PD5.Signal=FMC_NWE
PD6.Signal=GPIO_Output
PD7.GPIOParameters=GPIO_PuPd
PD7.GPIO_PuPd=GPIO_PULLDOWN
PD7.Signal=GPIO_Input
PE0.Signal=GPIO_Output
PE1.Signal=GPIO_Output
PE10.Signal=FMC_D7_DA7
PE11.Signal=GPIO_Output
PE12.Signal=GPIO_Output
PE15.Signal=GPIO_Output
PE2.GPIOParameters=GPIO_Speed
PE2.GPIO_Speed=GPIO_SPEED_FREQ_VERY_HIGH
PE2.Mode=Single Bank 1
PE2.Signal=QUADSPI_BK1_IO2
PE3.GPIOParameters=GPIO_PuPd
PE3.GPIO_PuPd=GPIO_PULLDOWN
PE3.Signal=GPIO_Input
PE4.GPIOParameters=GPIO_PuPd
PE4.GPIO_PuPd=GPIO_PULLDOWN
PE4.Signal=GPIO_Input
PE7.Signal=FMC_D4_DA4
PE8.Signal=FMC_D5_DA5
PE9.Signal=FMC_D6_DA6
PH0-OSC_IN\ (PH0).Mode=HSE-External-Oscillator
PH0-OSC_IN\ (PH0).Signal=RCC_OSC_IN
PH1-OSC_OUT\ (PH1).Mode=HSE-External-Oscillator
PH1-OSC_OUT\ (PH1).Signal=RCC_OSC_OUT
RCC.HSE_VALUE=24000000
RCC.SYSCLKFreq_VALUE=48000000
RCC.SYSCLKSource=RCC_SYSCLKSOURCE_PLLCLK
board=custom

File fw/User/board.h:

//
// Grimoire
// Copyright 2025 Wenting Zhang
//
// Permission is hereby granted, free of charge, to any person obtaining a copy
// of this software and associated documentation files (the "Software"), to deal
// in the Software without restriction, including without limitation the rights
// to use, copy, modify, merge, publish, distribute, sublicense, and/or sell
// copies of the Software, and to permit persons to whom the Software is
// furnished to do so, subject to the following conditions:
//
// The above copyright notice and this permission notice shall be included in
// all copies or substantial portions of the Software.
//
// THE SOFTWARE IS PROVIDED "AS IS", WITHOUT WARRANTY OF ANY KIND, EXPRESS OR
// IMPLIED, INCLUDING BUT NOT LIMITED TO THE WARRANTIES OF MERCHANTABILITY,
// FITNESS FOR A PARTICULAR PURPOSE AND NONINFRINGEMENT. IN NO EVENT SHALL THE
// AUTHORS OR COPYRIGHT HOLDERS BE LIABLE FOR ANY CLAIM, DAMAGES OR OTHER
// LIABILITY, WHETHER IN AN ACTION OF CONTRACT, TORT OR OTHERWISE, ARISING FROM,
// OUT OF OR IN CONNECTION WITH THE SOFTWARE OR THE USE OR OTHER DEALINGS IN THE
// SOFTWARE.
//
#pragma once

#include "pal_i2c.h"

#define LED_GRN         GPIOE, GPIO_PIN_0
#define LED_RED         GPIOE, GPIO_PIN_1

#define BTNCNT          3
#define BTN1            GPIOE, GPIO_PIN_4
#define BTN2            GPIOB, GPIO_PIN_5
#define BTN3            GPIOE, GPIO_PIN_3

#define BTN_PRESSED_LEVEL   1 // Active high

#define FPGA_CS         GPIOB, GPIO_PIN_12
#define FPGA_PROG       GPIOC, GPIO_PIN_10
#define FPGA_DONE       GPIOC, GPIO_PIN_11
#define FPGA_SUSP       GPIOC, GPIO_PIN_12

#define DP_PDN          GPIOD, GPIO_PIN_3
#define DP_HPD          GPIOD, GPIO_PIN_7
#define DP_ACTIVE       GPIOE, GPIO_PIN_6
#define DEC_RST         GPIOD, GPIO_PIN_6

#define HPD_EN          GPIOA, GPIO_PIN_9

#define TYPEC_ORI       GPIOA, GPIO_PIN_10
#define TCPC_INT        GPIOA, GPIO_PIN_15

#define EPD_PWREN       GPIOE, GPIO_PIN_11
#define EPD_POSEN       GPIOE, GPIO_PIN_12
#define EPD_THROT       GPIOD, GPIO_PIN_2

#define FL_EN           GPIOE, GPIO_PIN_15

#define VCOM_MEN        GPIOA, GPIO_PIN_2
#define VCOM_EN         GPIOA, GPIO_PIN_3

#define FPGA_SPI        &hspi2

#define PTN3460_I2C     &pi2c1
#define ADV7611_I2C     &pi2c1
#define FUSB302_I2C     &pi2c1
#define INA3221_I2C     &pi2c1

#define TYPEC_MB_ORI_INV    0
#define TYPEC_AUX_ORI_INV   0

#define PTN3460_I2C_ADDR    (0x60)
#define ADV7611_I2C_ADDR    (0x4C)
#define FUSB302_I2C_ADDR    (0x22)
#define INA3221_0_I2C_ADDR  (0x40)
#define INA3221_1_I2C_ADDR  (0x41)
#define INA3221_2_I2C_ADDR  (0x42)

// ADV7611 Sub addresses, make sure they don't conflict with anything else!
#define CEC_I2C_ADDR        (0x3F) // Default 0x40(0x80)
#define INFOFRAME_I2C_ADDR  (0x3E) // Default 0x3E(0x7C)
#define DPLL_I2C_ADDR       (0x26) // Default 0x26(0x4C)
#define KSV_I2C_ADDR        (0x32) // Default 0x32(0x64)
#define EDID_I2C_ADDR       (0x36) // Default 0x36(0x6C)
#define HDMI_I2C_ADDR       (0x34) // Default 0x34(0x68)
#define CP_I2C_ADDR         (0x23) // Default 0x22(0x44)

// For now, these resources are not shared among multiple threads, do not protect them
extern SPI_HandleTypeDef hspi2;
extern ADC_HandleTypeDef hadc1;
extern DAC_HandleTypeDef hdac1;
extern QSPI_HandleTypeDef hqspi;
extern TIM_HandleTypeDef htim1;

// GPIO operations are atomic, no need to protect
#define gpio_put        HAL_GPIO_WritePin
#define gpio_get        HAL_GPIO_ReadPin
#define sleep_ms(x)     vTaskDelay(pdMS_TO_TICKS(x))

#define spi_send(spi, buf, size) \
    HAL_SPI_Transmit(spi, buf, size, HAL_MAX_DELAY)
#define spi_send_dma(spi, buf, size) \
    HAL_SPI_Transmit_DMA(spi, buf, size)
#define spi_send_recv(spi, txbuf, rxbuf, size) \
    HAL_SPI_TransmitReceive(spi, txbuf, rxbuf, size, HAL_MAX_DELAY)

#define board_get_uid   HAL_GetUIDw0

size_t board_usb_get_serial(uint16_t desc_str1[], size_t max_chars);
void board_switch_spi_freq(SPI_HandleTypeDef *spi, uint32_t target);
void board_late_init(void); // Initialization only after RTOS has started
void sleep_us(uint32_t x);
void spi_wait_dma_complete(SPI_HandleTypeDef *spi);

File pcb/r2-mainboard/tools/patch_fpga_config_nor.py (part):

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
   **The net names look inverted and are not.** They are R1's, and they are
   host-centric: `FPGA_MOSI` is data *toward* the FPGA, so it lands on the FPGA's
   DIN pin and on the NOR's DO; `FPGA_MISO` is data *out of* the FPGA, so it
   lands on the FPGA's MOSI/CSI_B pin and drives the NOR's DI.  An on-sheet note
   says so, because this is the one thing on the sheet that reads wrong.

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                              "SPI_buswidth:1",
                  val_at=(83.82, 187.96))
    LX = 53.34                                    # label column, left of the part
    for pin, net in (("1", NOR_CS), ("6", "FPGA_SCLK"), ("5", "FPGA_MISO"),
                     ("2", "FPGA_MOSI")):
        px, py = nor.pin(pin)
        s.wire((px, py), (LX, py))
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                              "two briefly contend if software gets it wrong")
    s.wire(ser.pin("2"), node)
    s.wire((27.94, node[1]), ser.pin("1"))
    s.hlabel(27.94, node[1], "NOR_CS", shape="input", justify="right")

    # the same net reaches the FPGA's CSO_B ball, which the port left flagged
    s.wire(T3, (T3[0] + 12.7, T3[1]))
    s.label(T3[0] + 12.7, T3[1], NOR_CS)

    # ---- INIT_B ---------------------------------------------------------- #
    ip = s.place("Device:R", "R414", "4.7k", 101.6, 168.91, val_at=(93.98, 167.64),
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                             "error from 'still loading' when DONE never comes")
    s.power("+3V3", *ip.pin("1"))
    s.wire(ip.pin("2"), (101.6, 172.72), (113.03, 172.72))
    s.label(101.6, 172.72, "FPGA_INIT")
    s.hlabel(113.03, 172.72, "FPGA_INIT", shape="output")

    # ---- the note that stops the next reader mis-reading the bus --------- #
    # The A4 frame stops at ~197.5 mm and the title block owns x >= 177,
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
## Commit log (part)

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2025-10-16 Fix description about VCOM settings
2025-10-16 Skip empty lines when dumping wbf
2025-10-16 Update for new boards; Force reset when lost of signal
2025-11-23 Implement blanking and power-off
2025-11-24 Fix tick time calculation
2025-12-07 add the hash for current Git head to the 'ver' shell command
2025-12-15 Add provision for supporting touchscreen
2026-01-26 Disable VCOM when powering off
2026-01-26 Use absolute path for submodule
2026-02-27 Fix reboot loop when input source is not auto
2026-02-28 Update flash tool
2026-03-03 Update waveform tools to support multi-voltage panels
2026-05-09 add state tracking for PTN3460 to avoid race condition
    This fixes a bug where the USB PD task may try to send i2c commands to
    PTN3460 after it's being shut down, which causes fw to lock up
2026-05-10 add a few new filesystem commands scoped under 'fs'
    Some of the existing commands such as 'dump' and 'format' are also moved
    under the 'fs' umbrella for consistency and to reduce clutter at the
    top level
2026-05-10 add support for configuring custom bistream file names
    The code is backward compatible with existing config files.
2026-05-10 extend memory related info to show stats for heap as well
    The new 'mem [detail]' command shows the info from previous 'stacks'
    command and adds heap allocation stats.
2026-05-10 add compiler config for building run-from-RAM debug fw
    * DebugRAM build configuration is added in STM32CubeIDE. The default is
    still 'Debug', so the new config must be intentionally selected when
    building the firmware. The differences from the 'Debug' config are:
    * using STM32H750VBTX_RAM.ld linker script instead of _FLASH.ld
    * define USER_VECT_TAB_ADDRESS and VECT_TAB_SRAM; as far as I
    understand, this way the interrupt vectors table is placed in RAM
2026-06-28 Implement native low-power standby mode and DisplayPort wakeup
